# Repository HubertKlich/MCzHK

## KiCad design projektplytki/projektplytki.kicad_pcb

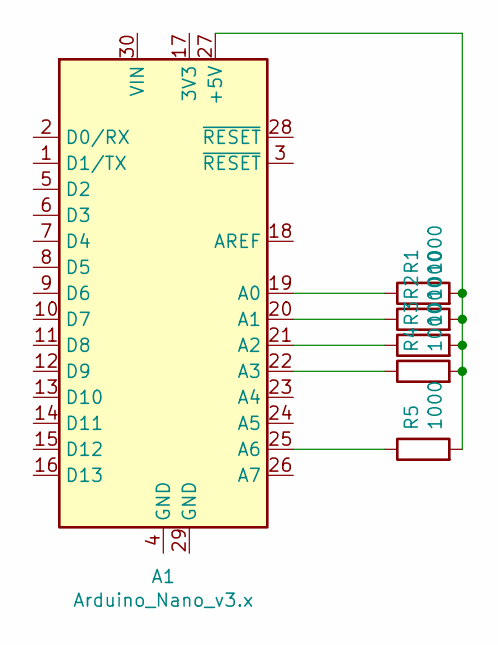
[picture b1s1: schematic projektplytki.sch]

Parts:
A1: Arduino_Nano_v3.x; Arduino_Nano
R1, R2, R3, R4, R5: 1000; R_Axial_DIN0207_L6.3mm_D2.5mm_P7.62mm_Horizontal

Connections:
unnamed: A1.19 (A0), R1.1
unnamed: A1.20 (A1), R2.1
unnamed: A1.21 (A2), R3.1
unnamed: A1.22 (A3), R4.1
unnamed: A1.25 (A6), R5.1
unnamed: A1.27 (+5V), R1.2, R2.2, R3.2, R4.2, R5.2

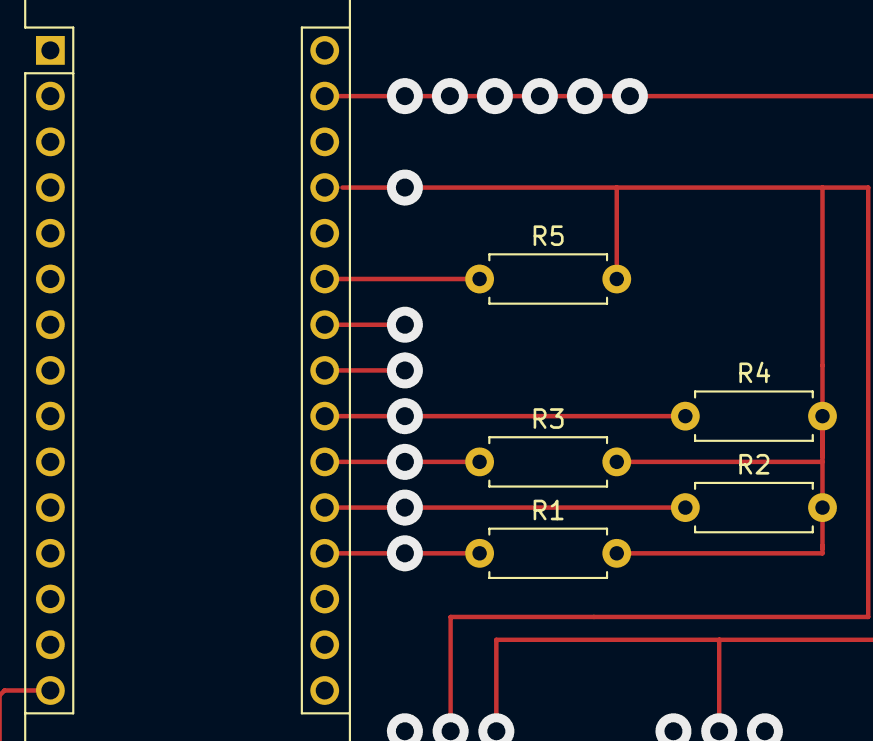
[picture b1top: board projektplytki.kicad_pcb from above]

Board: 2 copper layers, 6 parts (0 on the bottom side), 6 nets.

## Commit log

2021-03-07 Create ArduinoRekawica
    Poczatek
2021-03-15 Update ArduinoRekawica
2021-03-15 Create OdbiornikArduino
2021-04-22 Projekt plytki PCB
2021-10-28 Update OdbiornikArduino
